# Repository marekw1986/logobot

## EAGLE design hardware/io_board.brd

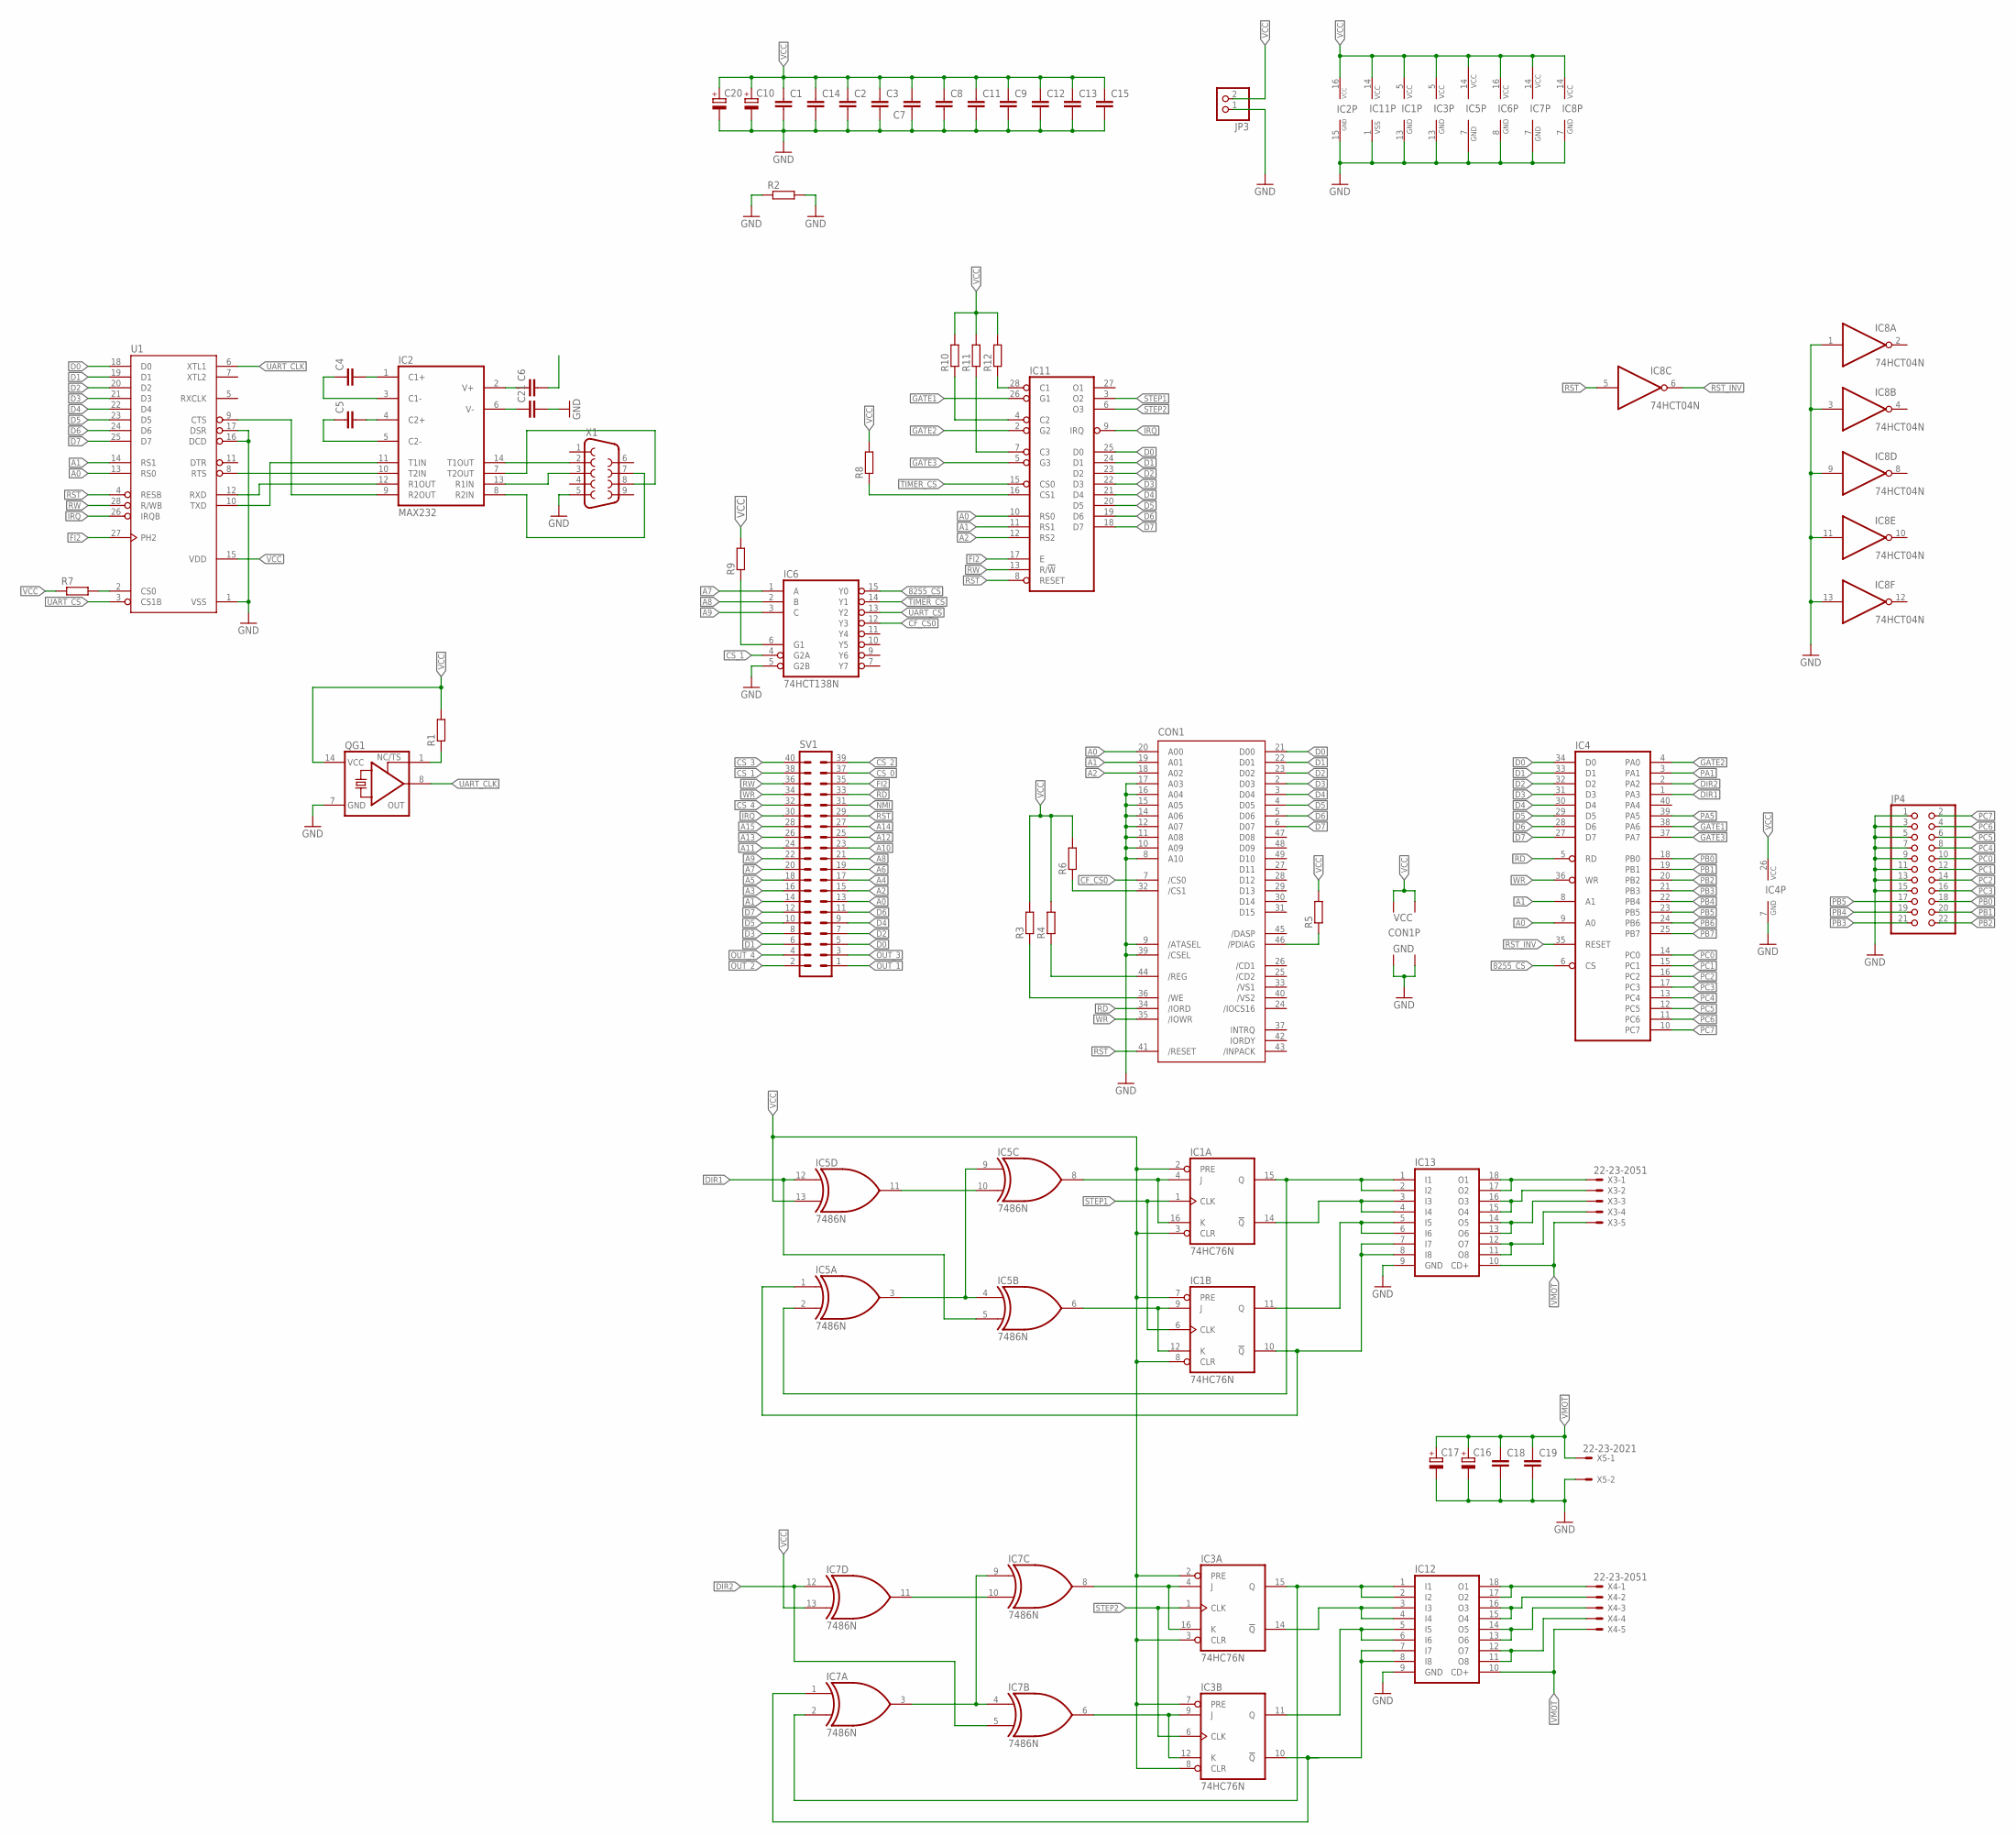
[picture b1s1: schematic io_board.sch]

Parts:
C1, C2, C3, C14: C-EUC1206; C1206
C4, C5, C6, C7, C8, C9, C12, C13, C15, C18, C19, C21: C-EUC0603; C0603
C10: CPOL-EUE5-10.5; E5-10,5
C11: C-EU050-024X044; C050-024X044
C16, C17: CPOL-EUE5-6; E5-6
C20: CPOL-EUSMCB; SMC_B
CON1: CF-CARD-IDE_MODE; MI20-50PD-SF
IC1, IC3: 74HC76N; DIL16
IC2: MAX232; DIL16
IC4: 8255A; DIL40
IC5, IC7: 7486N; DIL14
IC6: 74HCT138N; DIL16
IC8: 74HCT04N; DIL14
IC11: 6840; DIL28
IC12, IC13: ULN2803A; DIL18
JP3: PINHD-1X2/90; 1X02/90
JP4: PINHD-2X11; 2X11
QG1: XO-14; DIL14S
R1, R9: R-EU_R1206; R1206
R2: R-EU_M1206; M1206
R3, R4, R5, R6, R7, R10: R-EU_R0603; R0603
R8: R-EU_R0402; R0402
R11: R-EU_0204/7; 0204/7
R12: R-EU_0204/5; 0204/5
SV1: ML40L
U1: G65SC51P; DIP-28
X1: F09HP
X3, X4: 22-23-2051
X5: 22-23-2021

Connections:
8255_CS: IC4.6 (CS), IC6.15 (Y0)
A0: CON1.20 (A00), IC4.9 (A0), IC11.10 (RS0), SV1.13, U1.13 (RS0)
A1: CON1.19 (A01), IC4.8 (A1), IC11.11 (RS1), SV1.14, U1.14 (RS1)
A2: CON1.18 (A02), IC11.12 (RS2), SV1.15
A3: SV1.16
A4: SV1.17
A5: SV1.18
A6: SV1.19
A7: IC6.1 (A), SV1.20
A8: IC6.2 (B), SV1.21
A9: IC6.3 (C), SV1.22
A10: SV1.23
A11: SV1.24
A12: SV1.25
A13: SV1.26
A14: SV1.27
A15: SV1.28
CF_CS0: CON1.7 (/CS0), IC6.12 (Y3)
CS_0: SV1.37
CS_1: IC6.4 (G2A), SV1.38
CS_2: SV1.39
CS_3: SV1.40
CS_4: SV1.32
D0: CON1.21 (D00), IC4.34 (D0), IC11.25 (D0), SV1.5, U1.18 (D0)
D1: CON1.22 (D01), IC4.33 (D1), IC11.24 (D1), SV1.6, U1.19 (D1)
D2: CON1.23 (D02), IC4.32 (D2), IC11.23 (D2), SV1.7, U1.20 (D2)
D3: CON1.2 (D03), IC4.31 (D3), IC11.22 (D3), SV1.8, U1.21 (D3)
D4: CON1.3 (D04), IC4.30 (D4), IC11.21 (D4), SV1.9, U1.22 (D4)
D5: CON1.4 (D05), IC4.29 (D5), IC11.20 (D5), SV1.10, U1.23 (D5)
D6: CON1.5 (D06), IC4.28 (D6), IC11.19 (D6), SV1.11, U1.24 (D6)
D7: CON1.6 (D07), IC4.27 (D7), IC11.18 (D7), SV1.12, U1.25 (D7)
DIR1: IC4.1 (PA3), IC5.5 (I1), IC5.12 (I0)
DIR2: IC4.2 (PA2), IC7.5 (I1), IC7.12 (I0)
FI2: IC11.17 (E), SV1.35, U1.27 (PH2)
GATE1: IC4.38 (PA6), IC11.26 (G1)
GATE2: IC4.4 (PA0), IC11.2 (G2)
GATE3: IC4.37 (PA7), IC11.5 (G3)
IRQ: IC11.9 (IRQ), SV1.30, U1.26 (IRQB)
MOT1_PHASE1: IC1.15 (Q), IC5.2 (I1), IC13.1 (I1), IC13.2 (I2)
MOT1_PHASE2: IC1.14 (!Q), IC13.3 (I3), IC13.4 (I4)
MOT1_PHASE3: IC1.11 (Q), IC13.5 (I5), IC13.6 (I6)
MOT1_PHASE4: IC1.10 (!Q), IC5.1 (I0), IC13.7 (I7), IC13.8 (I8)
MOT1_PHASE5: IC3.15 (Q), IC7.2 (I1), IC12.1 (I1), IC12.2 (I2)
MOT1_PHASE6: IC3.14 (!Q), IC12.3 (I3), IC12.4 (I4)
MOT1_PHASE7: IC3.11 (Q), IC12.5 (I5), IC12.6 (I6)
MOT1_PHASE8: IC3.10 (!Q), IC7.1 (I0), IC12.7 (I7), IC12.8 (I8)
unnamed: QG1.1 (TS), R1.1
unnamed: IC2.13 (R1IN), X1.3
unnamed: IC2.7 (T2OUT), X1.8
unnamed: IC2.8 (R2IN), X1.7
unnamed: C4.2, IC2.1 (C1+)
unnamed: C5.2, IC2.4 (C2+)
unnamed: C5.1, IC2.5 (C2-)
unnamed: C4.1, IC2.3 (C1-)
unnamed: C6.1, IC2.2 (V+)
unnamed: C21.1, IC2.6 (V-)
unnamed: CON1.32 (/CS1), R6.1
unnamed: IC2.14 (T1OUT), X1.2
unnamed: R7.2, U1.2 (CS0)
unnamed: IC6.6 (G1), R9.1
unnamed: CON1.44 (/REG), R4.1
unnamed: CON1.36 (/WE), R3.1
unnamed: CON1.46 (/PDIAG), R5.1
unnamed: IC1.4 (J), IC1.16 (K), IC5.8 (O)
unnamed: IC5.10 (I1), IC5.11 (O)
unnamed: IC5.3 (O), IC5.4 (I0), IC5.9 (I0)
unnamed: IC1.9 (J), IC1.12 (K), IC5.6 (O)
unnamed: IC13.17 (O2), IC13.18 (O1), X3.1
unnamed: IC13.15 (O4), IC13.16 (O3), X3.2
unnamed: IC13.13 (O6), IC13.14 (O5), X3.3
unnamed: IC13.11 (O8), IC13.12 (O7), X3.4
unnamed: IC7.10 (I1), IC7.11 (O)
unnamed: IC7.3 (O), IC7.4 (I0), IC7.9 (I0)
unnamed: IC3.4 (J), IC3.16 (K), IC7.8 (O)
unnamed: IC3.9 (J), IC3.12 (K), IC7.6 (O)
unnamed: IC12.17 (O2), IC12.18 (O1), X4.1
unnamed: IC12.15 (O4), IC12.16 (O3), X4.2
unnamed: IC12.13 (O6), IC12.14 (O5), X4.3
unnamed: IC12.11 (O8), IC12.12 (O7), X4.4
unnamed: IC11.16 (CS1), R8.1
unnamed: IC11.4 (C2), R10.1
unnamed: IC11.7 (C3), R11.1
unnamed: IC11.28 (C1), R12.1
NMI: SV1.31
OUT_1: SV1.1
OUT_2: SV1.2
OUT_3: SV1.3
OUT_4: SV1.4
PA1: IC4.3 (PA1)
PA5: IC4.39 (PA5)
PB0: IC4.18 (PB0), JP4.18
PB1: IC4.19 (PB1), JP4.20
PB2: IC4.20 (PB2), JP4.22
PB3: IC4.21 (PB3), JP4.21
PB4: IC4.22 (PB4), JP4.19
PB5: IC4.23 (PB5), JP4.17
PB6: IC4.24 (PB6)
PB7: IC4.25 (PB7)
PC0: IC4.14 (PC0), JP4.10
PC1: IC4.15 (PC1), JP4.12
PC2: IC4.16 (PC2), JP4.14
PC3: IC4.17 (PC3), JP4.16
PC4: IC4.13 (PC4), JP4.8
PC5: IC4.12 (PC5), JP4.6
PC6: IC4.11 (PC6), JP4.4
PC7: IC4.10 (PC7), JP4.2
RD: CON1.34 (/IORD), IC4.5 (RD), SV1.33
RST: CON1.41 (/RESET), IC8.5 (I), IC11.8 (RESET), SV1.29, U1.4 (RESB)
RST_INV: IC4.35 (RESET), IC8.6 (O)
RW: IC11.13 (R/!W), SV1.36, U1.28 (R/WB)
RXD_TTL: IC2.12 (R1OUT), U1.12 (RXD)
STEP1: IC1.1 (CLK), IC1.6 (CLK), IC11.3 (O2)
STEP2: IC3.1 (CLK), IC3.6 (CLK), IC11.6 (O3)
TIMER_CS: IC6.14 (Y1), IC11.15 (CS0)
TXD_TTL: IC2.11 (T1IN), U1.10 (TXD)
UART_CLK: QG1.8 (OUT), U1.6 (XTL1)
UART_CS: IC6.13 (Y2), U1.3 (CS1B)
VCC: C1.1, C2.1, C3.1, C6.2, C7.2, C8.1, C9.1, C10.+, C11.1, C12.1, C13.1, C14.1, C15.1, C20.+, CON1.13 (VCC2), CON1.38 (VCC1), IC1.2 (PRE), IC1.3 (CLR), IC1.5 (VCC), IC1.7 (PRE), IC1.8 (CLR), IC2.16 (VCC), IC3.2 (PRE), IC3.3 (CLR), IC3.5 (VCC), IC3.7 (PRE), IC3.8 (CLR), IC4.26 (VCC), IC5.13 (I1), IC5.14 (VCC), IC6.16 (VCC), IC7.13 (I1), IC7.14 (VCC), IC8.14 (VCC), IC11.14 (VCC), JP3.2, QG1.14 (VCC), R1.2, R3.2, R4.2, R5.2, R6.2, R7.1, R8.2, R9.2, R10.2, R11.2, R12.2, U1.15 (VDD)
VMOT: C16.+, C17.+, C18.1, C19.1, IC12.10 (CD+), IC13.10 (CD+), X3.5, X4.5, X5.1
WR: CON1.35 (/IOWR), IC4.36 (WR), SV1.34

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
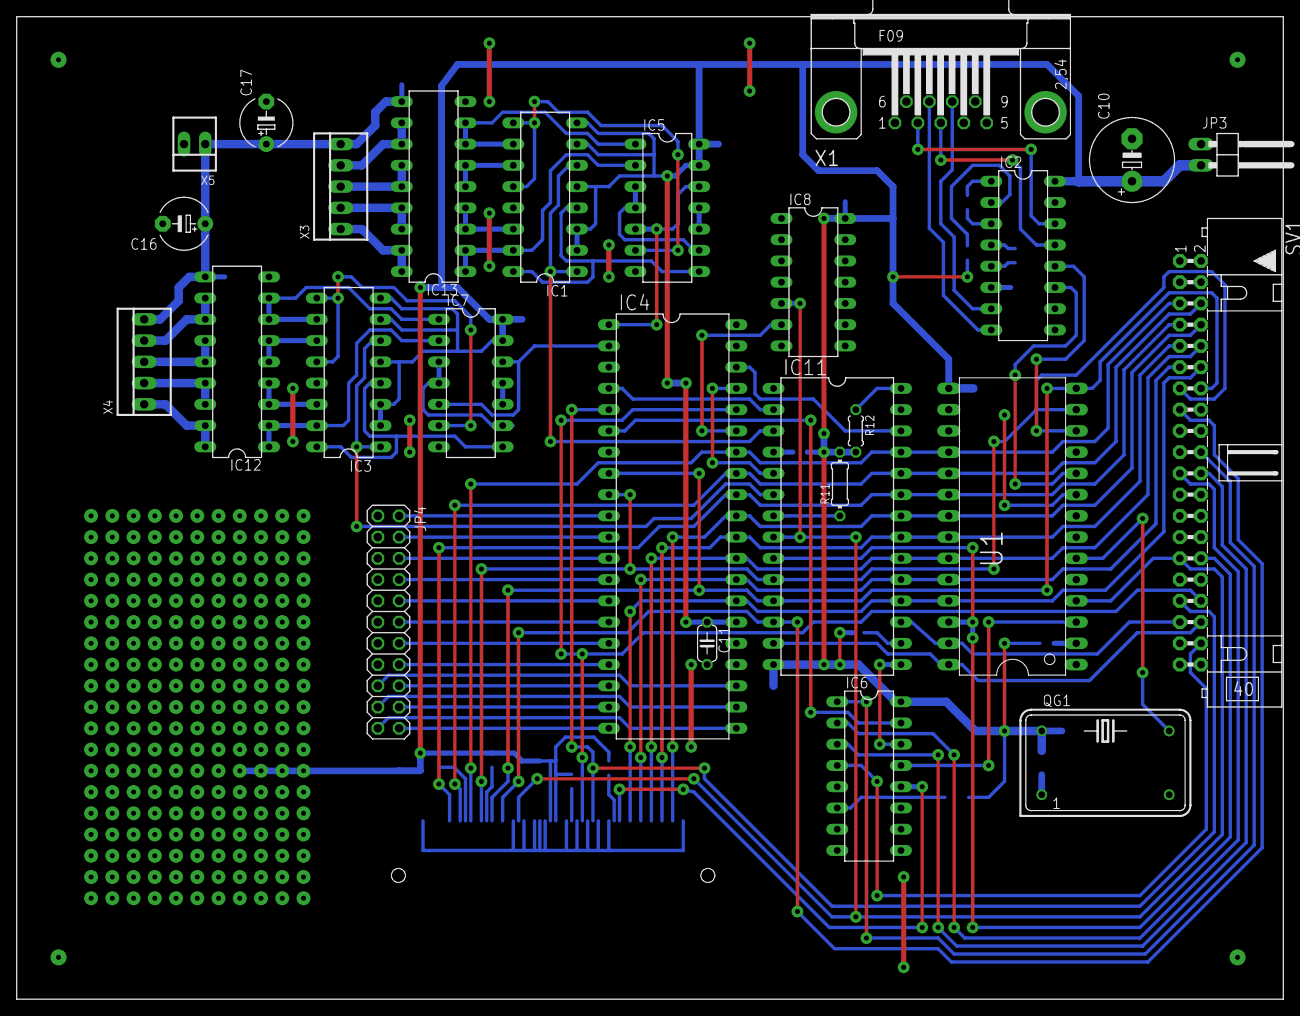
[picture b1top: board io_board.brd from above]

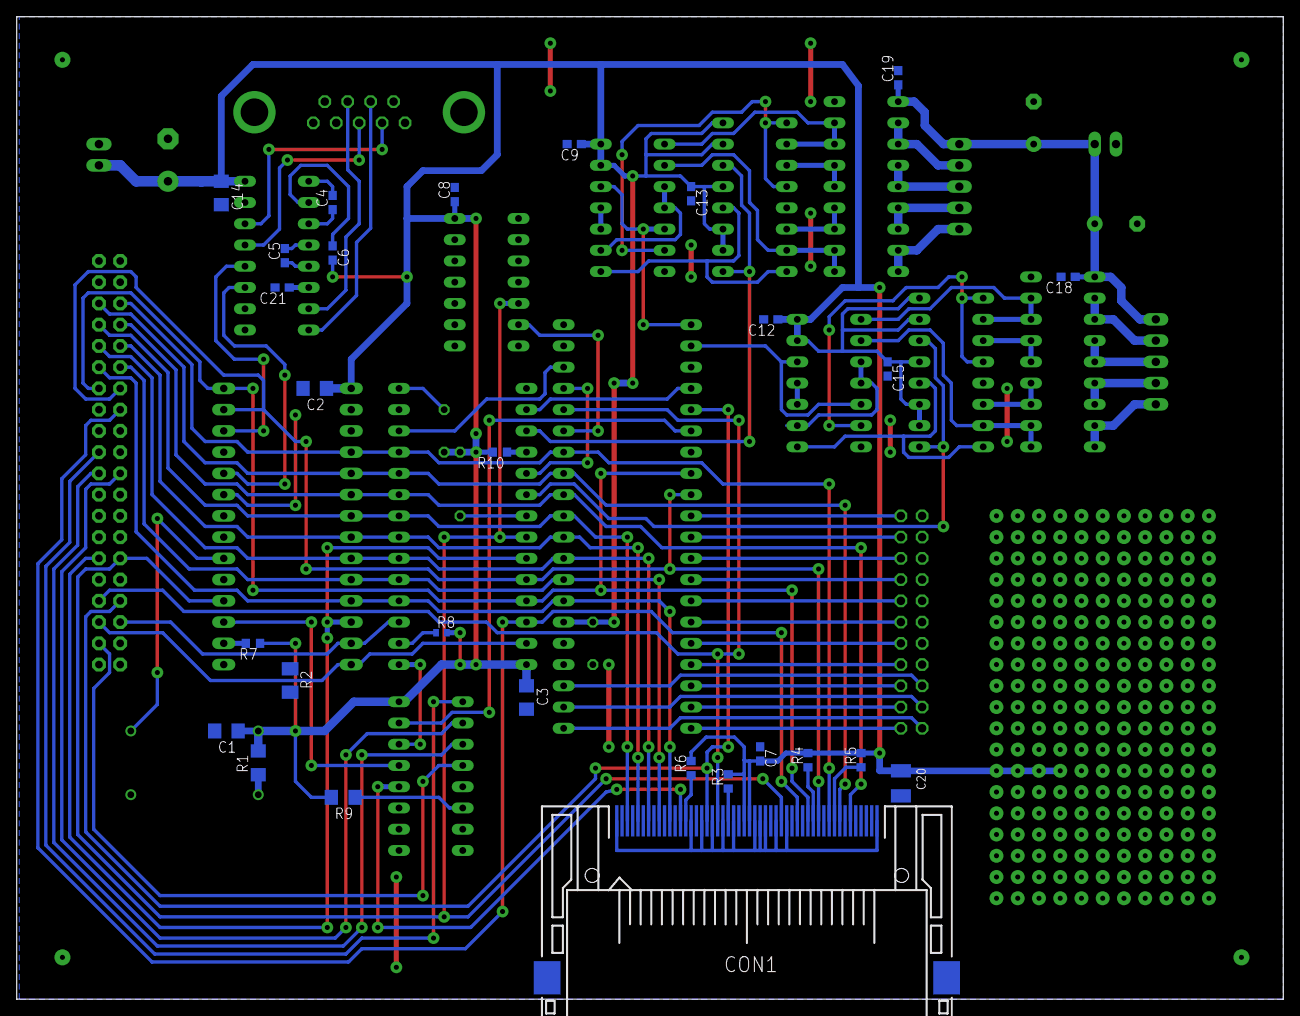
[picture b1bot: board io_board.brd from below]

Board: 2 copper layers, 151.4 x 117.5 mm, 54 parts (28 on the bottom side), 98 nets.

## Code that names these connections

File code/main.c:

//0x4000 - EEPROM
//0x6000 - CS0		LCD + BUTTONS
//		0x6000 - NOT USED
//		0x6080 - NOT USED
//		0x6100 - NOT USED
//		0x6180 - NOT USED
//		0x6200 - NOT USED
//		0x6280 - NOT USED
//		0x6300 - BUTTONS
//		0x6380 - HD44780 LCD

//0x6400 - CS1
//		0x6400 - 8255
//		0x6480 - TIMER
//		0x6500 - UART
//		0x6580 - CF
//		0x6600 - NOT USED
//		0x6680 - NOT USED
//		0x6700 - NOT USED
//		0x6780 - NOT USED

//0x6800 - CS2
//0x6C00 - CS3
//0x7000 - CS4
//0x7400 - CS5
//0x7800 - CS6
//0x7C00 - CS7

#include <stdio.h>
#include <stdint.h>
#include <stdlib.h>
#include <string.h>
#include <time.h>
#include <6502.h>
#include "config.h"
#include "hd44780.h"
#include "mos6551.h"
#include "mc6840.h"
#include "delay.h"
#include "io.h"

static char buffer[64];
static uint16_t number = 0;
static uint8_t timer = 0;
static uint8_t uart_timer = 0;

char* __fastcall__ utoa (unsigned val, char* buf, int radix);
char* __fastcall__ ultoa (unsigned long val, char* buf, int radix);
size_t __fastcall__ strlen (const char* s);


int main (void) {
	port_write(0x81);
	
	CONF_8255 = 0x80;			//Mode 0, PA, PB and PC is n output
	PA_8255 = 0x81; 			//(GATE3=1, GATE1=0, PA5=0. PA4=0, DIR1=0, DIR2=0, PA1=0, GATE2=1)
	PB_8255 = 0x00;				//All PB outputs low
	PC_8255 = 0x00;	 			//All PC outputs low

	mc6840_init();
	mos6551_init();
	hd44780_init();
	
	CLI();

	hd44780_gotoxy(0, 0);
	hd44780_puts("6502 is still alive!");
	hd44780_gotoxy(1, 0);
	hd44780_puts("Device designed by");
	hd44780_gotoxy(2, 0);
	hd44780_puts("Marek Wiecek SQ9RZI");
	
    MOTOR1_FREQ(20); //20 Hz
    MOTOR1_DIR_FORWARD;
    MOTOR1_START;

    MOTOR2_FREQ(40); //40 Hz
    MOTOR2_DIR_BACKWARD;
    MOTOR2_START;
    
	while(1) {
		if ( (uint8_t)(millis() - timer) > 12 ) {			//12x20ms
			timer = millis();
			port_tgl(0x84);						//Toggle both LEDs
			feed_hungry_watchdog();				//Reset watchdog
		
			hd44780_gotoxy(3, 0);
			hd44780_puts("                    ");		
			utoa(number,buffer, 10);
			hd44780_gotoxy(3, 0);
			hd44780_puts(buffer);
			number++;
			if (!(BTNS & BTN0)) { number += 50; }
		}			
		
		if ( (uint8_t)(millis() - uart_timer) > 40 ) {
			uart_timer = millis();
			mos6551_puts("Test\r\n");
		}	
			
		mos6551_handle_rx();
	}
	
	return 0;
}

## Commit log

2020-08-25 minor changes
2020-08-25 superfluous code removed
2020-08-25 wrong title
2020-09-12 some changes
2020-09-18 PCB added
2020-10-03 New version of CF driver
2020-10-05 watchdog changes
2020-10-05 CF fixes
2020-10-13 Added new peripherals
2020-10-13 Some fixes
2020-10-14 8255 configuration
2020-10-14 just minor changes
2020-10-14 macrodefinitions for motor
2020-10-18 IO board modified
2021-03-11 Cleaned
2021-03-12 gitignore
2021-03-25 MC6840 code fixed
